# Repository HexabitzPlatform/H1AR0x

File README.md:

# H1AR0x-Hardware
Hexabitz USB-C-to-UART Converter Module Hardware Design

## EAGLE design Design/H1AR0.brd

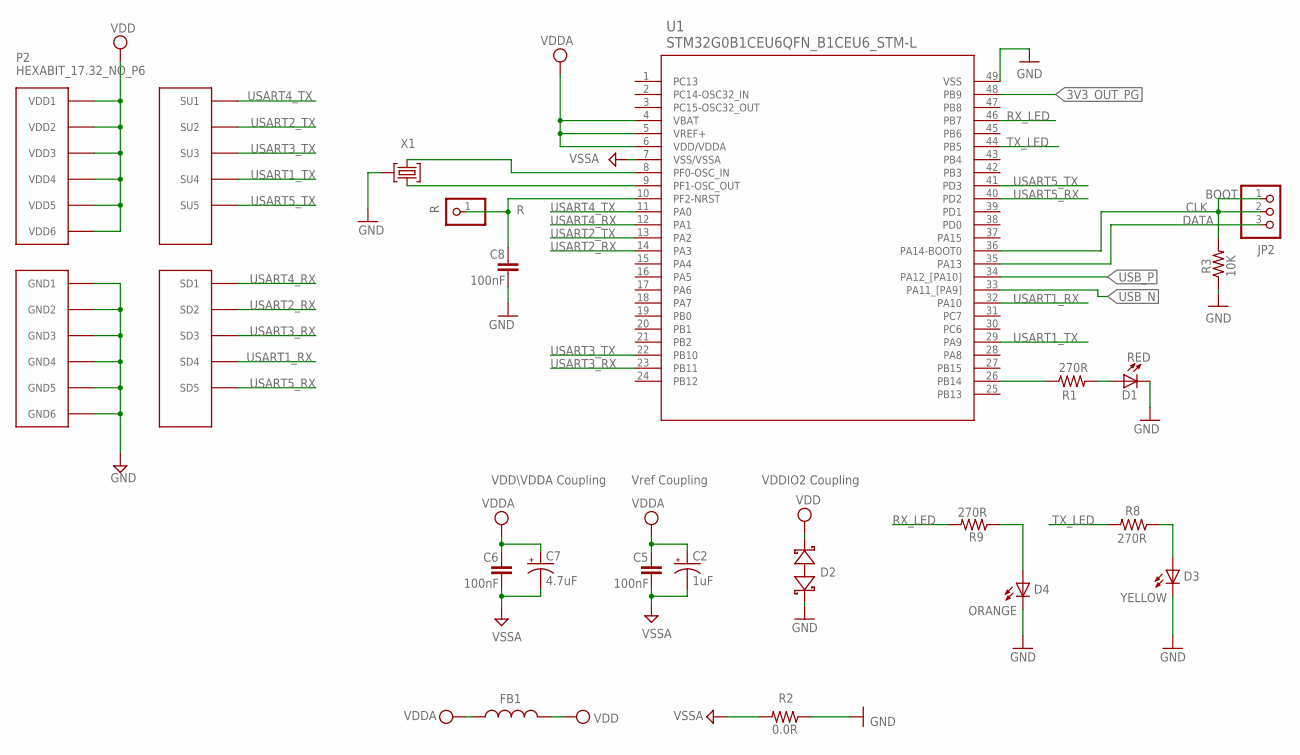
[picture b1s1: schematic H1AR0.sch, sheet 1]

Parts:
C2: 1uF; C-0805-POL
C5, C6, C8: 100nF; C-0603
C7: 4.7uF; C-0805-POL
D1: RED; VLMS1300-GS08; MPN VLMS1300-GS08
D2: BOURNS_CDSOD323-T03SCBOURNS_CDSOD323-T03SC_0_0; BOURNS_CDSOD323-T03SC_0
D3: YELLOW; VLMS1300-GS08
D4: ORANGE; VLMS1300-GS08
FB1: FB-TDK_MMZ1608Y300B; MPN MMZ1608Y300B
JP2: PINHD-1X3; 1X03
P2: HEXABIT_17.32_NO_P6
R: R; 1X01
R1, R8, R9: 270R; R-0603
R2: 0.0R; R-0603; MPN RC0603JR-070RL
R3: 10K; R-0603
TRIMBLE-LOGO1: HEXA-LOGO
U1: STM32G0B1CEU6QFN_B1CEU6_STM-L; QFN_B1CEU6_STM-L
X1: XTALL_CSTCE8M00G52

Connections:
3V3_OUT_PG: U1.48 (PB9); also elsewhere on the board
CLK: JP2.1, JP2.2, R3.2, U1.36 (PA14-BOOT0)
DATA: JP2.3, U1.35 (PA13)
GND: C8.2, D1.C, D2.1 (A), D3.C, D4.C, P2.PAD_PD7 (GND1), P2.PAD_PD8 (GND2), P2.PAD_PD9 (GND3), P2.PAD_PD10 (GND4), P2.PAD_PD11 (GND5), P2.PAD_PD12 (GND6), R2.1, R3.1, U1.49 (VSS), X1.P$2 (2); also elsewhere on the board
unnamed: R1.1, U1.26 (PB14)
unnamed: D1.A, R1.2
unnamed: C8.1, R.1, U1.10 (PF2-NRST)
unnamed: U1.9 (PF1-OSC_OUT), X1.P$1 (1)
unnamed: U1.8 (PF0-OSC_IN), X1.P$3 (3)
unnamed: D4.A, R9.1
unnamed: D3.A, R8.1
RX_LED: R9.2, U1.46 (PB7)
TX_LED: R8.2, U1.44 (PB5)
USART1_RX: P2.PAD_PD4 (SD4), U1.32 (PA10)
USART1_TX: P2.PAD_PU4 (SU4), U1.29 (PA9)
USART2_RX: P2.PAD_PD2 (SD2), U1.14 (PA3)
USART2_TX: P2.PAD_PU2 (SU2), U1.13 (PA2)
USART3_RX: P2.PAD_PD3 (SD3), U1.23 (PB11)
USART3_TX: P2.PAD_PU3 (SU3), U1.22 (PB10)
USART4_RX: P2.PAD_PD1 (SD1), U1.12 (PA1)
USART4_TX: P2.PAD_PU1 (SU1), U1.11 (PA0)
USART5_RX: P2.PAD_PD5 (SD5), U1.40 (PD2)
USART5_TX: P2.PAD_PU5 (SU5), U1.41 (PD3)
USB_N: U1.33 (PA11_[PA9]); also elsewhere on the board
USB_P: U1.34 (PA12_[PA10]); also elsewhere on the board
VDD: D2.2 (C), FB1.2, P2.PAD_PU7 (VDD1), P2.PAD_PU8 (VDD2), P2.PAD_PU9 (VDD3), P2.PAD_PU10 (VDD4), P2.PAD_PU11 (VDD5), P2.PAD_PU12 (VDD6); also elsewhere on the board
VDDA: C2.1 (+), C5.1, C6.1, C7.1 (+), FB1.1, U1.4 (VBAT), U1.5 (VREF+), U1.6 (VDD/VDDA)
VSSA: C2.2 (-), C5.2, C6.2, C7.2 (-), R2.2, U1.7 (VSS/VSSA)

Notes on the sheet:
Vref Coupling
VDDIO2 Coupling
VDD\VDDA Coupling
BOOT

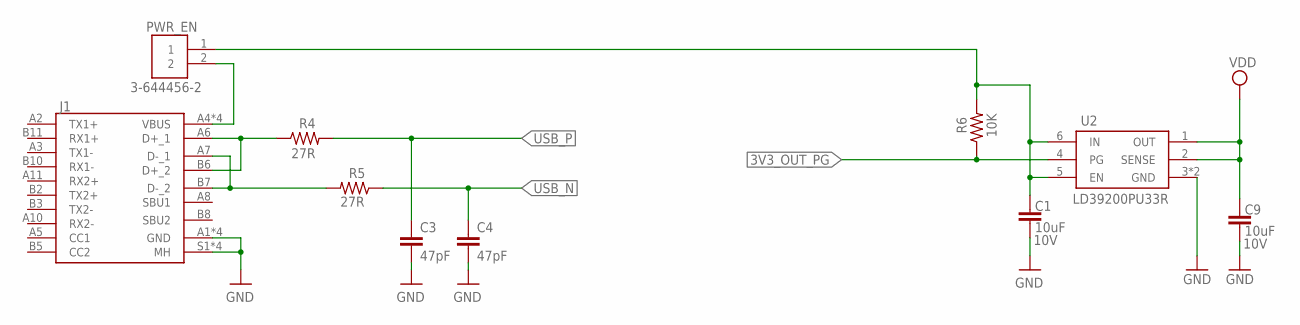
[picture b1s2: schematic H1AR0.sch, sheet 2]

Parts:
C1, C9: 10uF; C-0805; VOLTAGE_RATING 10V; MPN GRM187R61A226ME15
C3, C4: 47pF; C-0603
J1: 12401610E4#2A12401610E42A; AMPHENOL_12401610E4_2A
PWR_EN: 3-644456-2; TE_3-644456-2
R4, R5: 27R; R-0603; TOLERANCE 1%
R6: 10K; R-0603; TOLERANCE 1%
U2: LD39200PU33R; SON95P300X300X100-7N

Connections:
3V3_OUT_PG: R6.1, U2.4 (PG); also elsewhere on the board
D_N: J1.A7 (D-_1), J1.B7 (D-_2), R5.2
D_P: J1.A6 (D+_1), J1.B6 (D+_2), R4.1
GND: C1.1, C3.2, C4.2, C9.1, J1.A1 (GND), J1.A12 (GND), J1.B1 (GND), J1.B12 (GND), J1.S1 (MH), J1.S2 (MH), J1.S3 (MH), J1.S4 (MH), U2.3 (GND), U2.7 (GND); also elsewhere on the board
unnamed: C1.2, PWR_EN.1, R6.2, U2.5 (EN), U2.6 (IN)
unnamed: J1.A4 (VBUS), J1.A9 (VBUS), J1.B4 (VBUS), J1.B9 (VBUS), PWR_EN.2
USB_N: C4.1, R5.1; also elsewhere on the board
USB_P: C3.1, R4.2; also elsewhere on the board
VDD: C9.2, U2.1 (OUT), U2.2 (SENSE); also elsewhere on the board

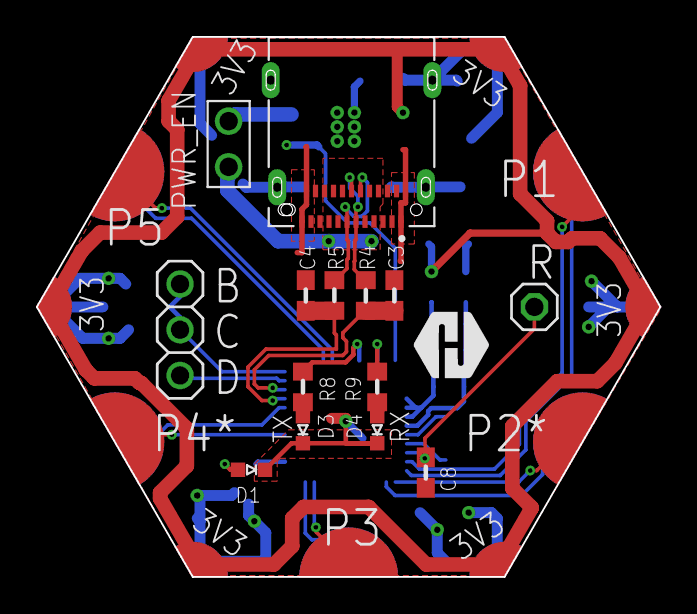
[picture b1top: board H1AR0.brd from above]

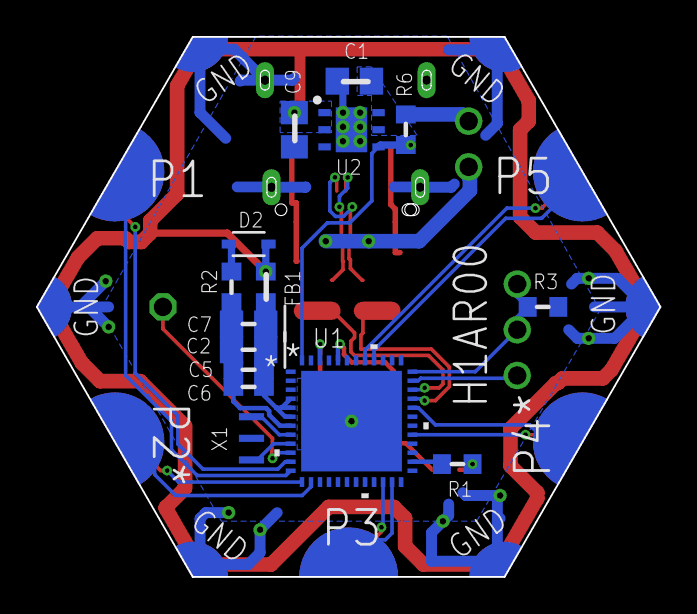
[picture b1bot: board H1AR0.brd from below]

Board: 2 copper layers, 34.6 x 30.0 mm, 31 parts (15 on the bottom side), 32 nets.

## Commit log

2024-12-14 All Finish, Reviewed Version
2025-01-15 Fix BOM

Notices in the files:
parts and their libraries:
COPYRIGHT: Copyright (C) 2021 Ultra Librarian. All rights reserved.
